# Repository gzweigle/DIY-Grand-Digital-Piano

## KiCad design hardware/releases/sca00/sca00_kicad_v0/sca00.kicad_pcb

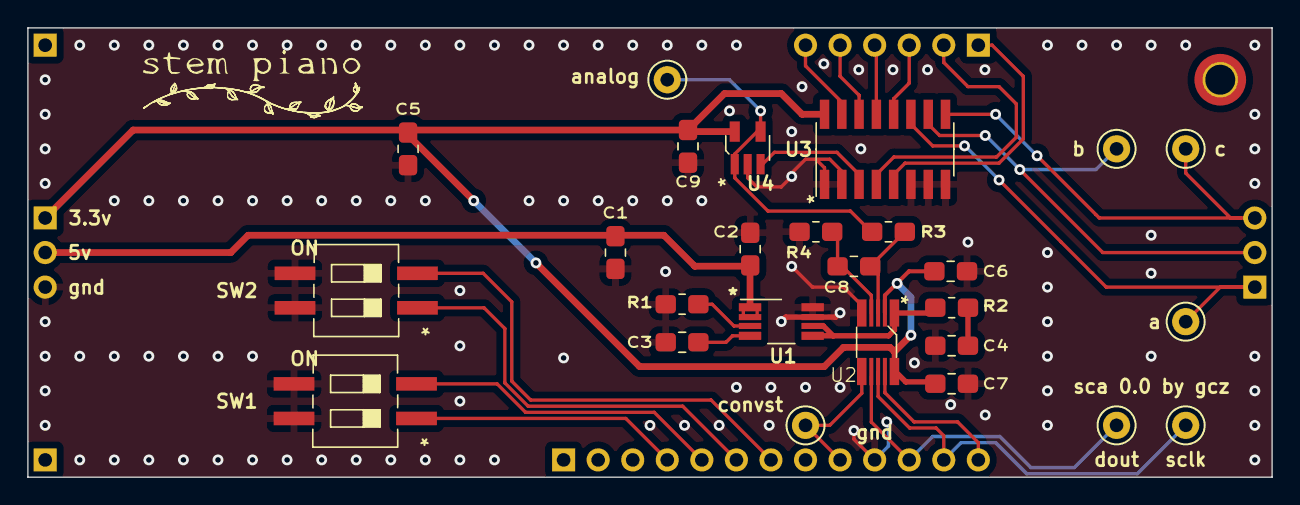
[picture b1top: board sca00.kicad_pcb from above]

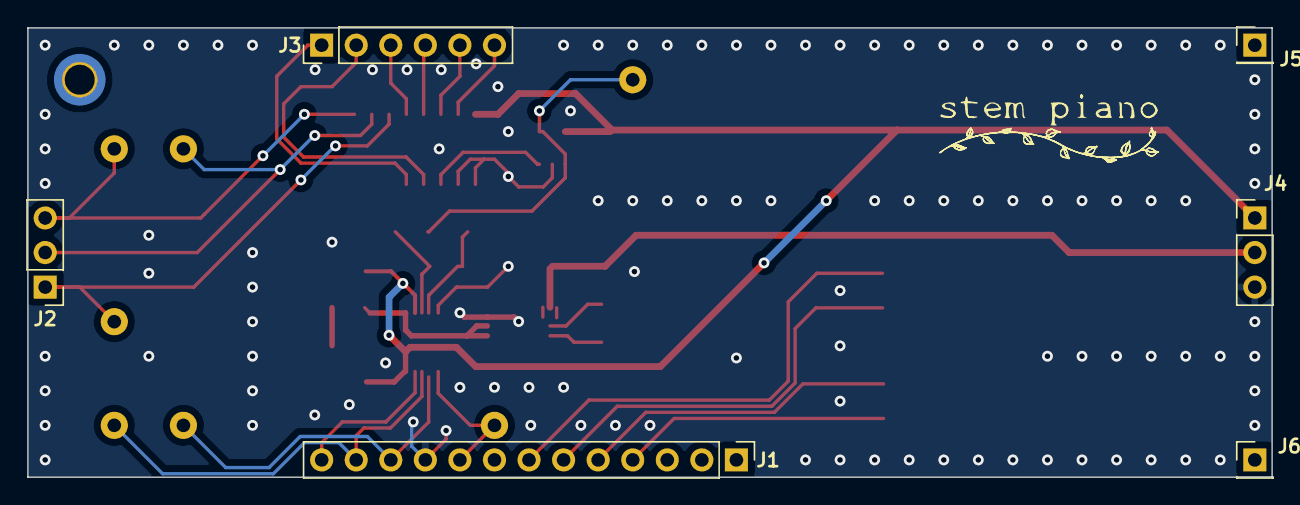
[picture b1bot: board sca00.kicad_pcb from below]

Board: 2 copper layers, 91.4 x 33.0 mm, 33 parts (6 on the bottom side), 28 nets.

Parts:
C1, C5: 10uF; C_0805_2012_1.18x1.45mm_medpad
C2, C3, C6, C7, C9: 1uF; C_0805_2012_1.18x1.45mm_medpad
C4: 47uF; C_0805_2012_1.18x1.45mm_medpad
C8: 500pF; C_0805_2012_1.18x1.45mm_medpad
H1: MountingHole; MountingHole_2.2mm_M2_DIN965_Pad_TopBottom
J1: Conn_01x13_Pin; PinHeader_1x13_P2.54mm_Vertical
J2, J4: Conn_01x03_Pin; PinHeader_1x03_P2.54mm_Vertical
J3: Conn_01x06_Pin; PinHeader_1x06_P2.54mm_Vertical
J5, J6: Conn_01x01_Pin; PinHeader_1x01_P2.54mm_Vertical
R1: 120K; R_0805_2012_1.20x1.40mm_medpad
R2: small; R_0805_2012_1.20x1.40mm_medpad
R3, R4: 50; R_0805_2012_1.20x1.40mm_medpad
SW1, SW2: SW_DIP_x02; SW_DIP_SPSTx02_Slide_medpad
TP1: analog; TestPoint_Keystone_5000-5004_Miniature
TP2: a; TestPoint_Keystone_5000-5004_Miniature
TP3: sclk; TestPoint_Keystone_5000-5004_Miniature
TP4: dout; TestPoint_Keystone_5000-5004_Miniature
TP5: convst; TestPoint_Keystone_5000-5004_Miniature
TP6: b; TestPoint_Keystone_5000-5004_Miniature
TP7: c; TestPoint_Keystone_5000-5004_Miniature
U1: REF6030; VSSOP-8_3.0x3.0mm_P0.65mm_medpads
U2: ADS8881; VSSOP-10_medpad
U3: SN74LV4051; SOIC-16_3.9x9.9mm_P1.27mm_medpad
U4: THS4281; SOT-23-5_medpad

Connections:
GND: C1.2, C2.2, C3.1, C4.1, C5.2, C6.1, C7.2, C9.1, J1.10, J4.3, R1.1, R4.2, SW1.3, SW1.4, SW2.3, SW2.4, U1.7 (GND_F), U1.8 (GND_S), U2.5 (GDN), U3.1 (Y4), U3.2 (Y6), U3.6 (INH), U3.7 (GND), U3.8 (GND), U4.2 (V-)
unnamed: C4.2, R2.1
unnamed: J1.4, SW1.1
unnamed: J1.5, SW1.2
unnamed: J1.6, SW2.1
unnamed: J1.7, SW2.2
unnamed: J1.9, TP5.1, U2.6 (CONVST)
unnamed: J1.11, TP4.1, U2.7 (DOUT)
unnamed: J1.12, TP3.1, U2.8 (SCLK)
unnamed: J1.13, U2.9 (DIN)
unnamed: J2.1, TP2.1, U3.11 (A)
unnamed: J2.2, TP6.1, U3.10 (B)
unnamed: J2.3, TP7.1, U3.9 (C)
unnamed: J3.1, U3.5 (Y5)
unnamed: J3.2, U3.4 (Y7)
unnamed: J3.3, U3.12 (Y3)
unnamed: J3.4, U3.13 (Y0)
unnamed: J3.5, U3.14 (Y1)
unnamed: J3.6, U3.15 (Y2)
unnamed: C5.1, C6.2, C7.1, C9.2, J4.1, U2.2 (AVDD), U2.10 (DVDD), U3.16 (VCC), U4.5 (V+)
unnamed: C1.1, C2.1, J4.2, U1.1 (VIN), U1.2 (EN)
unnamed: C3.2, U1.4 (FLT)
unnamed: R2.2, U1.5 (OUT_S), U1.6 (OUT_F), U2.1 (REF)
unnamed: R1.2, U1.3 (SS)
unnamed: C8.1, R4.1, U2.4 (AINN)
unnamed: C8.2, R3.2, U2.3 (AINP)
unnamed: U3.3 (COM), U4.3 (IN+)
unnamed: R3.1, TP1.1, U4.1 (OUT), U4.4 (IN-)

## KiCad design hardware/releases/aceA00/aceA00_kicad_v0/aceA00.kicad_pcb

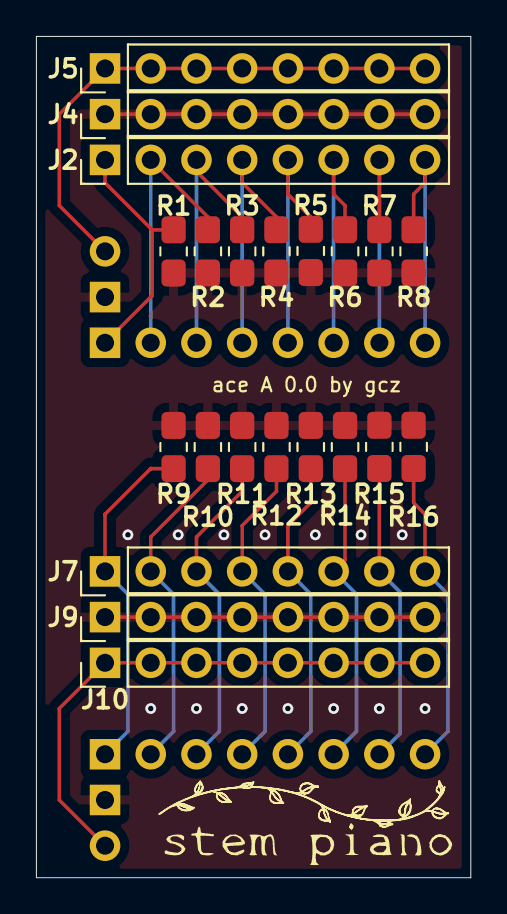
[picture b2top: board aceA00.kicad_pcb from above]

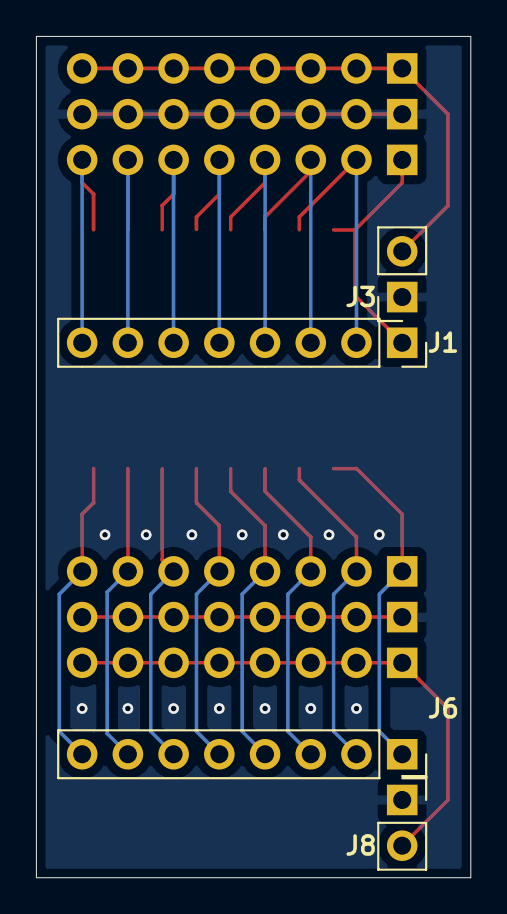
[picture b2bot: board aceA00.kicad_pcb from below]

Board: 2 copper layers, 24.1 x 46.7 mm, 26 parts (4 on the bottom side), 19 nets.

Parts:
J1, J6: Conn_01x08_Socket; PinSocket_1x08_P2.54mm_Vertical
J2, J4, J5, J7, J9, J10: Conn_01x08_Pin; PinHeader_1x08_P2.54mm_Vertical
J3, J8: Conn_01x02_Socket; PinSocket_1x02_P2.54mm_Vertical
R1, R2, R3, R4, R5, R6, R7, R8, R9, R10, R11, R12, R13, R14, R15, R16: R; R_0805_2012_1.20x1.40mm_medpad

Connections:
GND: J3.1, J4.1, J4.2, J4.3, J4.4, J4.5, J4.6, J4.7, J4.8, J8.1, J9.1, J9.2, J9.3, J9.4, J9.5, J9.6, J9.7, J9.8, R1.2, R2.2, R3.2, R4.2, R5.2, R6.2, R7.2, R8.2, R9.2, R10.2, R11.2, R12.2, R13.2, R14.2, R15.2, R16.2
unnamed: J1.1, J2.1, R1.1
unnamed: J1.2, J2.2, R2.1
unnamed: J1.3, J2.3, R3.1
unnamed: J1.4, J2.4, R4.1
unnamed: J1.5, J2.5, R5.1
unnamed: J1.6, J2.6, R6.1
unnamed: J1.7, J2.7, R7.1
unnamed: J1.8, J2.8, R8.1
unnamed: J3.2, J5.1, J5.2, J5.3, J5.4, J5.5, J5.6, J5.7, J5.8
unnamed: J6.1, J7.1, R9.1
unnamed: J6.2, J7.2, R10.1
unnamed: J6.3, J7.3, R11.1
unnamed: J6.4, J7.4, R12.1
unnamed: J6.5, J7.5, R13.1
unnamed: J6.6, J7.6, R14.1
unnamed: J6.7, J7.7, R15.1
unnamed: J6.8, J7.8, R16.1
unnamed: J8.2, J10.1, J10.2, J10.3, J10.4, J10.5, J10.6, J10.7, J10.8
